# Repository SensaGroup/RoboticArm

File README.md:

# SENSA - Robotic Arm 

Genral repository for files pertaining to the robotic arm that is part of SENSA GROUP education.  

## Description
The PCB interfaces the microcontroller with 5 stepper drivers and 5 encoders. 

## Features
- Main controller: ESP32WROOM-U.
- Wifi.
- Bluetooth.
- Programming over USB C. 
- 2x TB6600 Drivers. 
- 3x pinouts for general stepstick drivers. 
- 5x AMT102 encoder inputs. 
- Software (TBD)

## Pictures

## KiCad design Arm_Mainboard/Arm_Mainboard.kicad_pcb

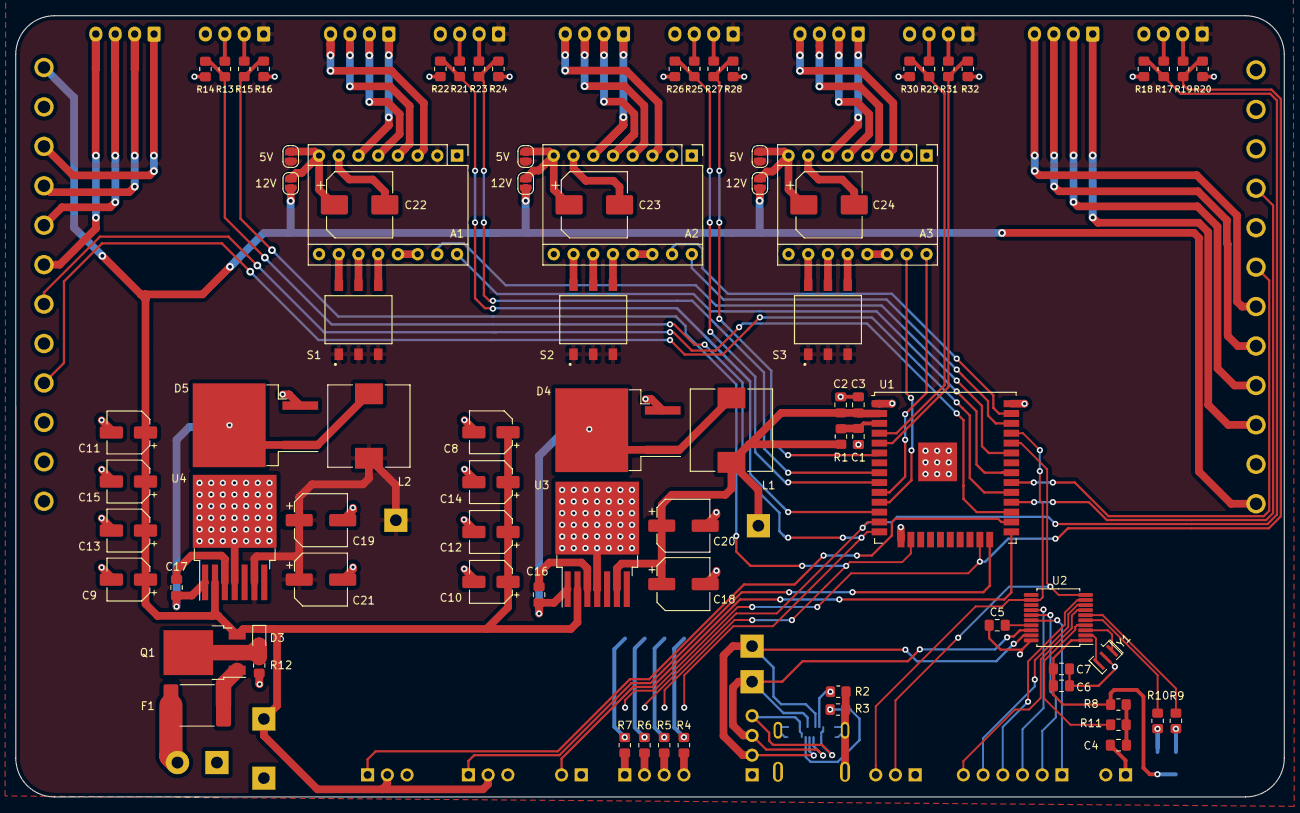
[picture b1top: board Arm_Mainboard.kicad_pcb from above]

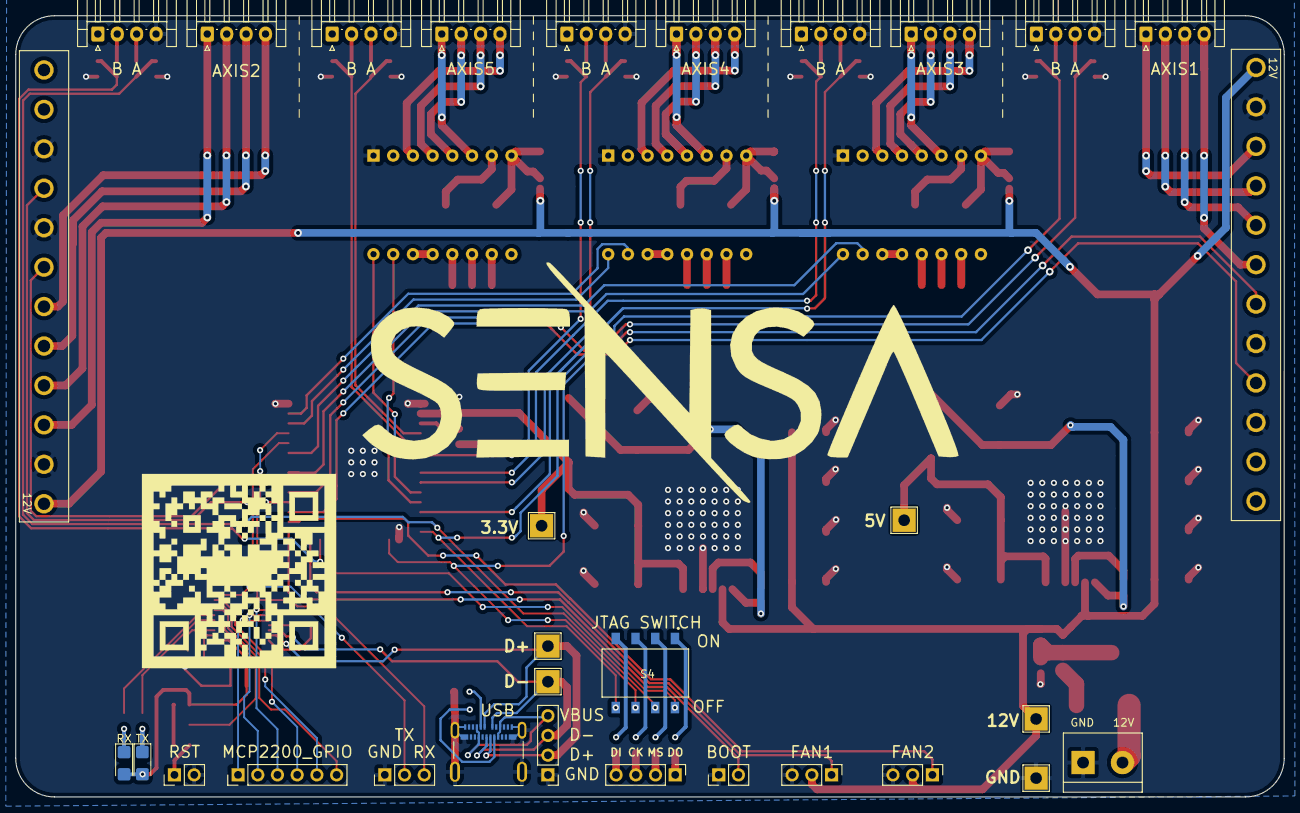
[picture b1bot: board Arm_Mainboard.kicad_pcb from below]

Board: 2 copper layers, 163.4 x 100.6 mm, 111 parts (31 on the bottom side), 109 nets.

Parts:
3.3V: VDD33; TestPoint_THTPad_3.0x3.0mm_Drill1.5mm
5V, 5V#2, 5V#3, 12V, 12V#2, 12V#3: 12V; SolderJumper-2_P1.3mm_Open_RoundedPad1.0x1.5mm
5V#4: VDD5; TestPoint_THTPad_3.0x3.0mm_Drill1.5mm
12V#4: V_IN; TestPoint_THTPad_3.0x3.0mm_Drill1.5mm
A1, A2, A3: Pololu_Breakout_A4988; Pololu_Breakout-16_15.2x20.3mm
AXIS1: CONN_NEMA23_1; JST_EH_S4B-EH_1x04_P2.50mm_Horizontal
C1, C3: 10uF; C_0805_2012Metric_Pad1.18x1.45mm_HandSolder
C2, C4: 0.1uF; C_0805_2012Metric_Pad1.18x1.45mm_HandSolder
C5: 470nF; C_0805_2012Metric_Pad1.18x1.45mm_HandSolder
C6, C7: 100nF; C_0805_2012Metric_Pad1.18x1.45mm_HandSolder
C8, C9: 15uF; CP_Elec_5x5.3
C10, C11, C12, C13, C14, C15: CP; CP_Elec_5x5.3
C16, C17: 0.01uF; C_0805_2012Metric_Pad1.18x1.45mm_HandSolder
C18, C19, C20, C21: 180uF; CP_Elec_6.3x5.9
C22, C23, C24: 100uF; CP_Elec_8x10
D3: D_Zener; D_SOD-323
D4, D5: D_Schottky; TO-263-2_TabPin1
D+: D+; TestPoint_THTPad_3.0x3.0mm_Drill1.5mm
D-: D-; TestPoint_THTPad_3.0x3.0mm_Drill1.5mm
F1: Fuse; Fuse_2920_7451Metric
GND: GND; TestPoint_THTPad_3.0x3.0mm_Drill1.5mm
J2: JTAG; PinHeader_1x04_P2.54mm_Vertical
J4: USB PINOUT; PinHeader_1x04_P2.54mm_Vertical
J6: UART; PinHeader_1x03_P2.54mm_Vertical
J7: BOOT OPTION; PinHeader_1x02_P2.54mm_Vertical
J8: POWER; TerminalBlock_bornier-2_P5.08mmCOPY
J9: FAN HEADER 1; PinHeader_1x03_P2.54mm_Vertical
J10: FAN HEADER 2; PinHeader_1x03_P2.54mm_Vertical
J14, J22, J26: CONN; JST_EH_S4B-EH_1x04_P2.50mm_Horizontal
J16: CONN_NEMA23_2; JST_EH_S4B-EH_1x04_P2.50mm_Horizontal
J19: NEMA23_2; Molex_12PIN
J20: NEMA23_1; Molex_12PIN
J27: ENC_AXIS1; JST_EH_S4B-EH_1x04_P2.50mm_Horizontal
J28: ENC_AXIS2; JST_EH_S4B-EH_1x04_P2.50mm_Horizontal
J29: ENC_AXIS3; JST_EH_S4B-EH_1x04_P2.50mm_Horizontal
J30: ENC_AXIS4; JST_EH_S4B-EH_1x04_P2.50mm_Horizontal
J31: ENC_AXIS5; JST_EH_S4B-EH_1x04_P2.50mm_Horizontal
L1, L2: 22uH; L_10.4x10.4_H4.8
MCP2200_GPIO: GPIO_PINOUT; PinHeader_1x06_P2.54mm_Vertical
Q1: P_CH MOSFET; TO-252-3_TabPin2
R1: 1K; R_0805_2012Metric_Pad1.20x1.40mm_HandSolder
R2, R3: 5K1; R_0805_2012Metric_Pad1.20x1.40mm_HandSolder
R4, R5, R6, R7, R9, R10: 100R; R_0805_2012Metric_Pad1.20x1.40mm_HandSolder
R8, R12: 10K; R_0805_2012Metric_Pad1.20x1.40mm_HandSolder
R11: 470R; R_0805_2012Metric_Pad1.20x1.40mm_HandSolder
R13, R15, R17, R19, R21, R23, R25, R27, R29, R31: 2K; R_0805_2012Metric_Pad1.20x1.40mm_HandSolder
R14, R16, R18, R20, R22, R24, R26, R28, R30, R32: 3K9; R_0805_2012Metric_Pad1.20x1.40mm_HandSolder
RST: RST; PinHeader_1x02_P2.54mm_Vertical
RX: LED; D_1206_3216Metric_Castellated
S1, S2, S3: DIP SWITCH; SW_DS04-254-2-03BK-SMT
S4: JTAG SELECTOR; SW_DS04-254-2-04BK-SMT
TX: LED; D_1206_3216Metric_Castellated
U1: ESP32-WROOM-32U
U2: MCP2200-I-SS; SSOP-20_5.3x7.2mm_P0.65mm
U3: LM2678SX-3.3/NOPB; TO-263-7_TabPin4
U4: LM2678S-5.0/NOPB; TO-263-7_TabPin4
USB : 105450-0101; MOLEX_105450-0101
Y1: Resonator; Resonator_SMD_muRata_CSTxExxV-3Pin_3.0x1.1mm

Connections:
+12V: 12V.1, 12V#2.1, 12V#3.1, 12V#4.1, C8.1, C9.1, C10.1, C11.1, C12.1, C13.1, C14.1, C15.1, D3.1, J9.2, J10.2, J19.12, J20.12, Q1.3, U3.2, U4.2
/BOOT: J7.2, U1.25
/DIR-NEMA11: A3.16, U1.10
/DIR-NEMA14_1: A1.16, U1.31
/DIR-NEMA14_2: A2.16, U1.36
/DIR-NEMA23_1: J20.4, U1.29
/DIR-NEMA23_2: J19.4, U1.28
/E1A: R13.2, R14.1, S4.4B, U1.14
/E1B: R15.2, R16.1, S4.3B, U1.16
/E2A: R17.2, R18.1, S4.2B, U1.13
/E2B: R19.2, R20.1, S4.1B, U1.23
/E3A: R21.2, R22.1, U1.12
/E3B: R23.2, R24.1, U1.8
/E4A: R25.2, R26.1, U1.9
/E4B: R27.2, R28.1, U1.6
/E5A: R29.2, R30.1, U1.4
/E5B: R31.2, R32.1, U1.5
/FAN1: J9.1, U1.24
/FAN2: J10.1, U1.26
/Interfaces/D+: D+.1, J4.2, U2.19, USB.A6, USB.B6
/Interfaces/D-: D-.1, J4.3, U2.18, USB.A7, USB.B7
/Interfaces/V_BUS: C6.2, C7.2, J4.4, R8.1, RX.2, TX.2, U2.1, USB.A4, USB.A9, USB.B4, USB.B9
/MTCK: R5.2, S4.3A
/MTDI: R4.2, S4.4A
/MTDO: R7.2, S4.1A
/MTMS: R6.2, S4.2A
/RoboticArmActuators/MS1-NEMA11: A3.10, S3.1B
/RoboticArmActuators/MS1-NEMA14_1: A1.10, S1.1B
/RoboticArmActuators/MS1-NEMA14_2: A2.10, S2.1B
/RoboticArmActuators/MS2-NEMA11: A3.11, S3.2B
/RoboticArmActuators/MS2-NEMA14_1: A1.11, S1.2B
/RoboticArmActuators/MS2-NEMA14_2: A2.11, S2.2B
/RoboticArmActuators/MS3-NEMA11: A3.12, S3.3B
/RoboticArmActuators/MS3-NEMA14_1: A1.12, S1.3B
/RoboticArmActuators/MS3-NEMA14_2: A2.12, S2.3B
/RoboticArmActuators/V_MOT: 5V.2, 5V#2.2, 5V#3.2, 12V.2, 12V#2.2, 12V#3.2, A1.8, A2.8, A3.8, C22.1, C23.1, C24.1
/RoboticArmPower/V_IN: F1.1, J8.2
/STEP-NEMA11: A3.15, U1.11
/STEP-NEMA14_1: A1.15, U1.33
/STEP-NEMA14_2: A2.15, U1.37
/STEP-NEMA23_1: J20.6, U1.27
/STEP-NEMA23_2: J19.6, U1.30
/U_RX: J6.3, U1.35, U2.12
/U_TX: J6.2, U1.34, U2.10
GND: A1.1, A1.7, A2.1, A2.7, A3.1, A3.7, C1.1, C2.2, C3.2, C5.1, C6.1, C7.1, C8.2, C9.2, C10.2, C11.2, C12.2, C13.2, C14.2, C15.2, C18.2, C19.2, C20.2, C21.2, C22.2, C23.2, C24.2, D4.2, D5.2, GND.1, J4.1, J6.1, J7.1, J8.1, J9.3, J10.3, J19.3, J19.5, J19.11, J20.3, J20.5, J20.11, J27.4, J28.4, J29.4, J30.4, J31.4, R2.1, R3.1, R12.1, R14.2, R16.2, R18.2, R20.2, R22.2, R24.2, R26.2, R28.2, R30.2, R32.2, RST.2, U1.1, U1.15, U1.38, U1.39, U2.20, U3.4, U4.4, USB.A1, USB.A12, USB.B1, USB.B12, USB.S1, USB.S2, USB.S3, USB.S4, Y1.2
unnamed: A1.3, J14.4
unnamed: A1.4, J14.3
unnamed: A1.5, J14.2
unnamed: A1.6, J14.1
unnamed: A1.13, A1.14
unnamed: A2.3, J22.4
unnamed: A2.4, J22.3
unnamed: A2.5, J22.2
unnamed: A2.6, J22.1
unnamed: A2.13, A2.14
unnamed: A3.3, J26.4
unnamed: A3.4, J26.3
unnamed: A3.5, J26.2
unnamed: A3.6, J26.1
unnamed: A3.13, A3.14
unnamed: C1.2, R1.1, U1.3
unnamed: C4.1, RST.1
unnamed: C4.2, R8.2, R11.2
unnamed: C5.2, U2.17
unnamed: C16.1, D4.1, L1.2, U3.1
unnamed: C16.2, U3.3
unnamed: C17.1, D5.1, L2.2, U4.1
unnamed: C17.2, U4.3
unnamed: R9.1, RX.1
unnamed: R10.1, TX.1
unnamed: D3.2, Q1.2, R12.2
unnamed: F1.2, Q1.1
unnamed: R2.2, USB.A5
unnamed: R3.2, USB.B5
unnamed: J2.1, R7.1
unnamed: J2.2, R6.1
unnamed: J2.3, R5.1
unnamed: J2.4, R4.1
unnamed: MCP2200_GPIO.1, U2.16
unnamed: MCP2200_GPIO.2, U2.15
unnamed: MCP2200_GPIO.3, U2.14
unnamed: MCP2200_GPIO.4, U2.9
unnamed: MCP2200_GPIO.5, U2.8
unnamed: MCP2200_GPIO.6, U2.7
unnamed: J16.1, J19.10
unnamed: J16.2, J19.9
unnamed: J16.3, J19.8
unnamed: J16.4, J19.7
unnamed: AXIS1.1, J20.10
unnamed: AXIS1.2, J20.9
unnamed: AXIS1.3, J20.8
unnamed: AXIS1.4, J20.7
unnamed: J27.2, R15.1
unnamed: J27.3, R13.1
unnamed: J28.2, R19.1
unnamed: J28.3, R17.1
unnamed: J29.2, R23.1
unnamed: J29.3, R21.1
unnamed: J30.2, R27.1
unnamed: J30.3, R25.1
unnamed: J31.2, R31.1
unnamed: J31.3, R29.1
unnamed: R9.2, U2.6
unnamed: R10.2, U2.5
unnamed: R11.1, U2.4
unnamed: U2.2, Y1.3
unnamed: U2.3, Y1.1
VDD5: 5V.1, 5V#2.1, 5V#3.1, 5V#4.1, A1.2, A2.2, A3.2, C19.1, C21.1, J27.1, J28.1, J29.1, J30.1, J31.1, L2.1, S1.1A, S1.2A, S1.3A, S2.1A, S2.2A, S2.3A, S3.1A, S3.2A, S3.3A, U4.6
VDD33: 3.3V.1, C2.1, C3.1, C18.1, C20.1, L1.1, R1.2, U1.2, U3.6

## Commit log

2021-08-02 Started schematic
2021-10-12 gerbers
2021-11-09 Update with pictures
